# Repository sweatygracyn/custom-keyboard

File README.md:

Gracyn's micro keyboard

BOM:
1 SEEEDUINO XIAO RP2040
4x cherry mx 1 switches
2x SK6812-MINI-E LED
4x same screws as orpheuspad and corresponding nuts

Schematic:

pcb:

3d model:

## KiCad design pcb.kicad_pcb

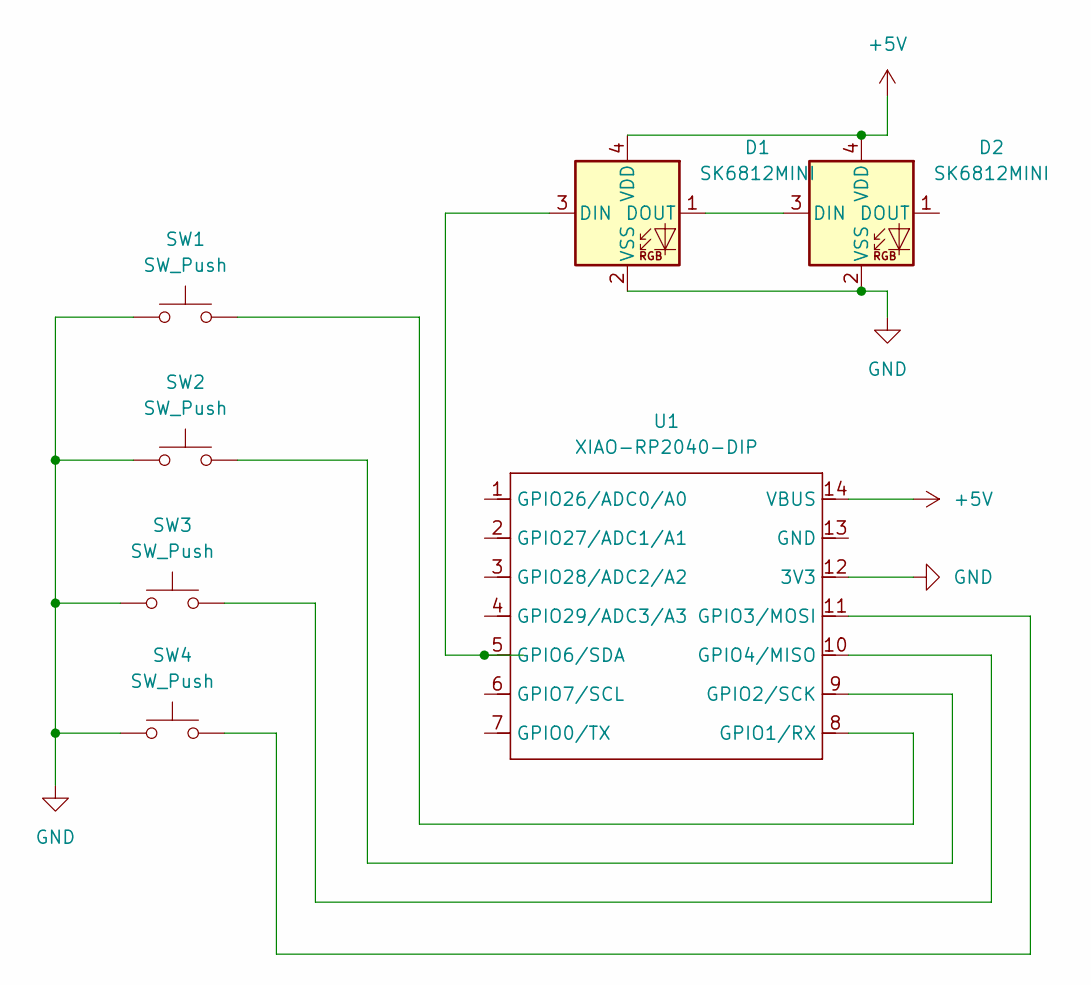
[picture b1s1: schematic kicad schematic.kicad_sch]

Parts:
D1, D2: SK6812MINI; LED_SK6812MINI_PLCC4_3.5x3.5mm_P1.75mm
SW1, SW2, SW3, SW4: SW_Push; SW_Cherry_MX_1.00u_PCB
U1: XIAO-RP2040-DIP

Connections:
+5V: D1.4 (VDD), D2.4 (VDD), U1.14 (VBUS)
GND: D1.2 (VSS), D2.2 (VSS), SW1.1, SW2.1, SW3.1, SW4.1, U1.12 (3V3)
unnamed: D1.3 (DIN), U1.5 (GPIO6/SDA)
unnamed: D1.1 (DOUT), D2.3 (DIN)
unnamed: SW1.2, U1.8 (GPIO1/RX)
unnamed: SW2.2, U1.9 (GPIO2/SCK)
unnamed: SW4.2, U1.11 (GPIO3/MOSI)
unnamed: SW3.2, U1.10 (GPIO4/MISO)

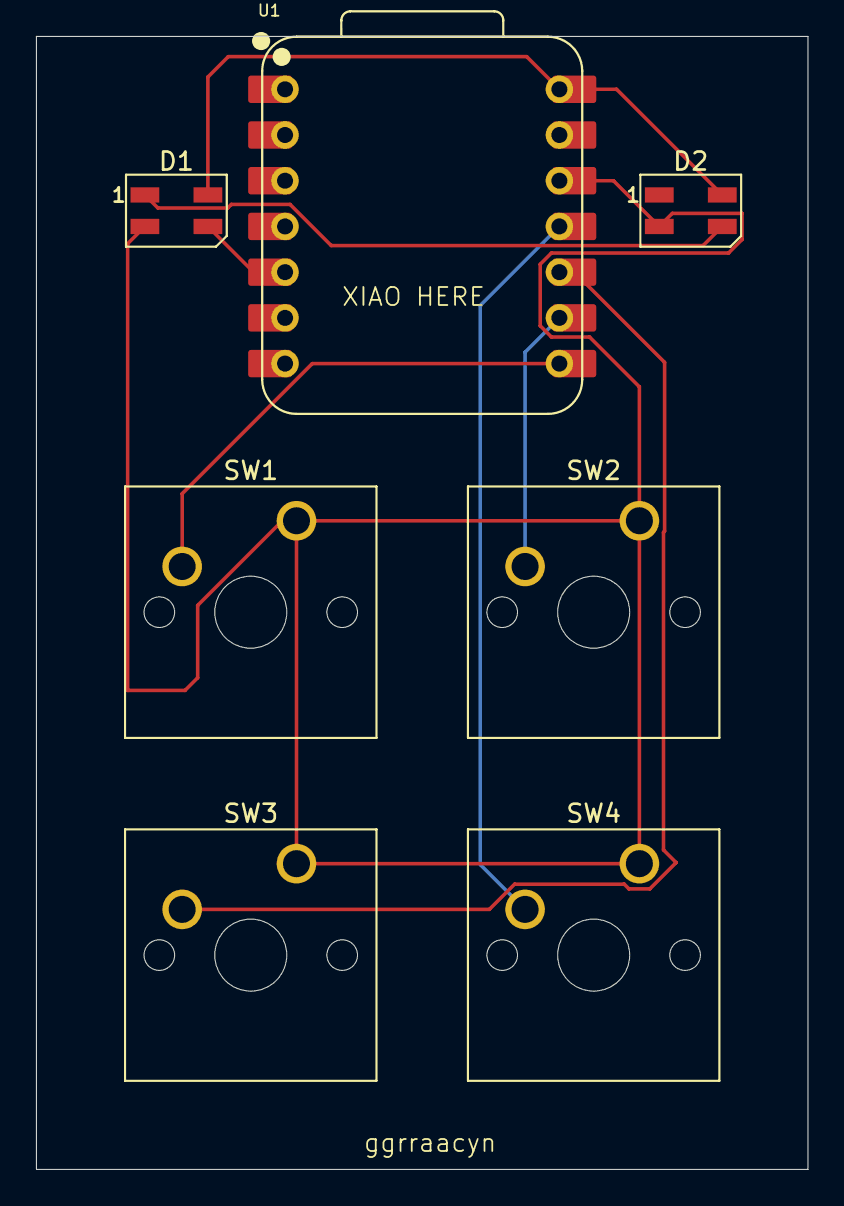
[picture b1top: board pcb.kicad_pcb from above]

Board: 2 copper layers, 42.9 x 62.9 mm, 7 parts (0 on the bottom side), 8 nets.

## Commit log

2025-12-05 README.md
